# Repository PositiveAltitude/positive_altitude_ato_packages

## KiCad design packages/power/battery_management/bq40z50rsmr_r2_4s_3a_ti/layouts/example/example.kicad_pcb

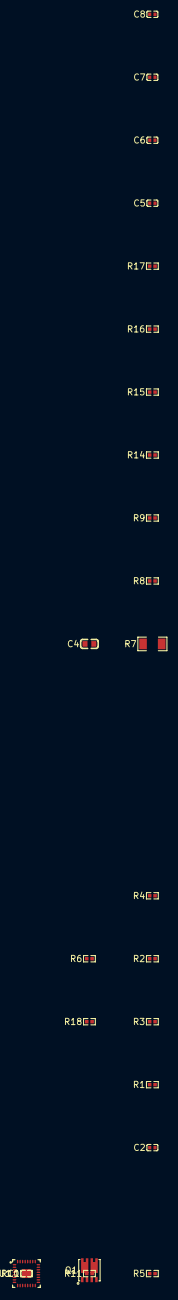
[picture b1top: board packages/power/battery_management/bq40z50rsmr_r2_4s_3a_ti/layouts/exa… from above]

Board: 2 copper layers, 25 parts (0 on the bottom side), 21 nets, no tracks yet.

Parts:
C1, C2, C5, C6, C7, C8: C0402
C4: C0603
Q1: DFN-8_L3.3-W3.3-P0.75-TL
R1, R2, R3, R4, R5, R6, R8, R9, R10, R11, R14, R15, R16, R17, R18: R0402
R7: R1206
U1: VQFN-32_L4.0-W4.0-P0.40-TL-EP1.4_2

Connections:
1: Q1.4, R1.1, R2.2
2: Q1.2, R3.1, R4.2
CHG: R2.1, U1.31
DSG: R4.1, U1.28
SMBC: R10.2, U1.19
SMBD: R11.2, U1.18
fet_common: Q1.5, Q1.8
frontend-1: C1.1, R5.1, U1.23
frontend-1-1: C4.1, U1.1
hv: Q1.3, R1.2, R6.1
lv: R7.2, R9.1
pack_filtered: R6.2, U1.27
raw_battery-hv: C1.2, Q1.1, R3.2, R5.2, R17.1, R18.1, U1.24, U1.32
raw_battery-lv: C4.2, C5.2, R7.1, R8.1, U1.9, U1.10, U1.11, U1.12, U1.13, U1.16, U1.17, U1.25, U1.33
srn_filtered: C2.2, R8.2, U1.6
srp_filtered: C2.1, R9.2, U1.8
vc1_filtered: C5.1, C6.2, R14.2, U1.5
vc2_filtered: C6.1, C7.2, R15.2, U1.4
vc3_filtered: C7.1, C8.2, R16.2, U1.3
vc4_filtered: C8.1, R17.2, U1.2
vcc_filtered: R18.2, U1.26

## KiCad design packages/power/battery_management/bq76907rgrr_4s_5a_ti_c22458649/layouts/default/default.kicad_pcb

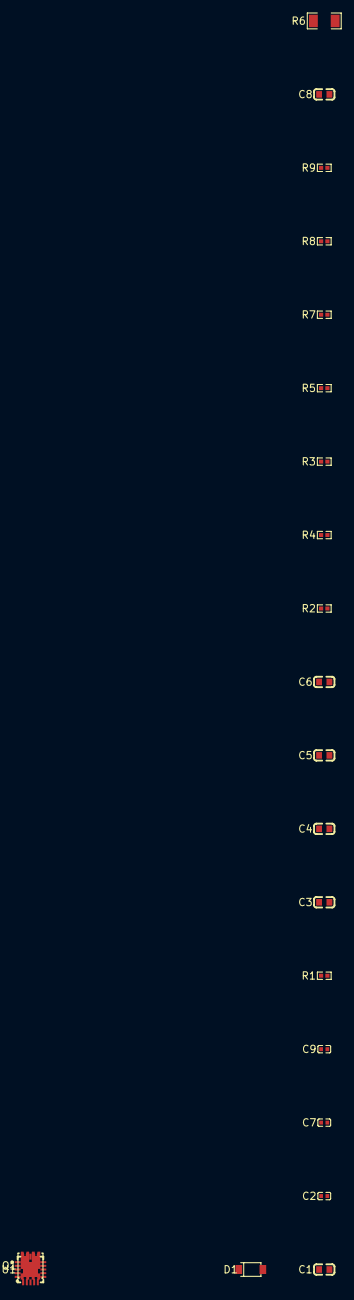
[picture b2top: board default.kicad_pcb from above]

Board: 2 copper layers, 21 parts (0 on the bottom side), 18 nets, no tracks yet.

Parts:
C1, C8: 1µF; C0603
C2, C7, C9: 100nF; C0402
C3, C4, C5, C6: 220nF; C0603
D1: Vf 0.45V; SOD-123_L2.7-W1.6-LS3.7-RD
Q1: DFN-8_L3.3-W3.3-P0.75-TL
R1: 10Ω; R0402
R2, R4: 100kΩ; R0402
R3, R5, R7, R8, R9: 100Ω; R0402
R6: 1mΩ; R1206
U1: VQFN-20_L3.5-W3.5-P0.50-TL-EP2.1

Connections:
2: Q1.2, R4.1, R5.2
4: Q1.4, R2.1, R3.2
CHG: R3.1, U1.10
DSG: R5.1, U1.9
anode: C6.1, D1.2, U1.18
cathode: D1.1, R1.1
cell_2_filter-power-hv: C3.1, C4.2, U1.3, U1.4
cell_3_filter-power-hv: C4.1, C5.2, U1.1, U1.2
cell_4_filter-power-hv: C5.1, C6.2, U1.19, U1.20
current_sense_filter-power-hv: C7.1, R8.2, U1.6
current_sense_filter-power-lv: C7.2, R7.2, U1.7
fet_common: Q1.5, Q1.8
hv: C1.1, C2.1, R1.2, U1.16, U1.17
lv: C1.2, C2.2, C8.2, C9.2, R6.1, R7.1, R9.1, U1.8, U1.11, U1.21
pack-lv: Q1.3, R2.2
regout_bulk-power-hv: C8.1, U1.15
sense_node: Q1.1, R4.2, R6.2, R8.1
vc0_filter_cap-power-hv: C3.2, C9.1, R9.2, U1.5

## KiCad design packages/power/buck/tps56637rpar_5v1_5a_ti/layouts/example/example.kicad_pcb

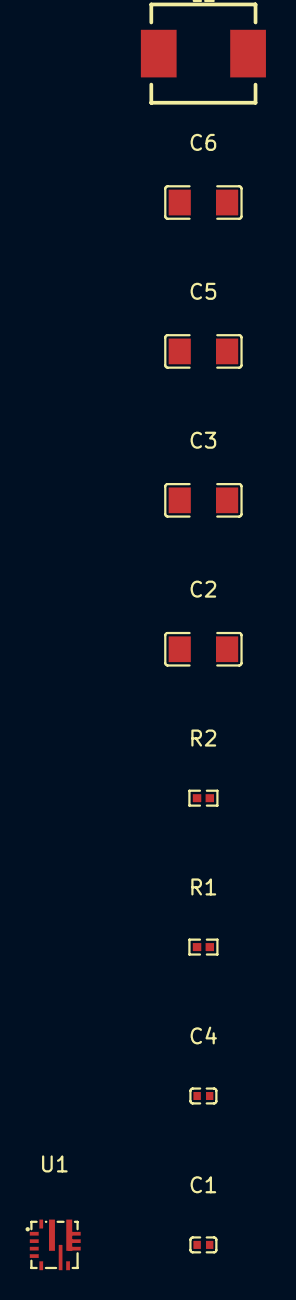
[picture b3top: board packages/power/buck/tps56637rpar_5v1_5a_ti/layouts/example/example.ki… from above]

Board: 2 copper layers, 10 parts (0 on the bottom side), 6 nets, no tracks yet.

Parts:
C1, C4: C0402
C2, C3, C5, C6: C1206
L1: IND-SMD_L7.0-W6.6
R1, R2: R0402
U1: VQFN-HR-10_L3.0-W3.0_RPA

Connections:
BOOT: C1.1, U1.7
FB: R1.1, R2.2, U1.2
GND: C2.2, C3.2, C4.2, C5.2, C6.2, R1.2, U1.3, U1.9
SW: C1.2, L1.1, U1.6
VIN: C2.1, C3.1, C4.1, U1.8
hv: C5.1, C6.1, L1.2, R2.1
